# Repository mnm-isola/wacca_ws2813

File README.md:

# WACCA WS2813 LED PCB Replacement

---

# WARNING: USE AT YOUR OWN RISK

---

## BOM (for use with WS2813E / WS2813B-V4 or below)

| Footprint | Parts                  | Size | Value  | LCSC    | Remark                                        |
| --------- | ---------------------- | ---- | ------ | ------- | --------------------------------------------- |
| C1-C8     | Decoupling Capacitors  | 0805 | 100nF  | C49678  |                                               |
| C9        | Electrolytic Capacitor | TBD  | 1000uF | TBD     | Optional. THT on rev1, SMD on later revisions |
| CN1,CN2   | JST XA 3 pin           |      |        | C265055 | B03B-XASK-1(LF)(SN)                           |
| CN3       | JST XA 4 pin           |      |        | C264994 | B04B-XASK-1(LF)(SN)                           |
| D1-D8     | Worldsemi WS2813E      |      |        | C160214 |                                               |
| R1,R2     |                        | 0805 | 100R   | C17408  |                                               |
| U1,U2     | MMBD1503A              |      |        | C242273 |                                               |

---

## BOM (for use with WS2813B-V5)

| Footprint | Parts                  | Size | Value  | LCSC    | Remark                                        |
| --------- | ---------------------- | ---- | ------ | ------- | --------------------------------------------- |
| C1-C8     |                        |      |        |         | WS2813B-V5 do not require decoupling caps     |
| C9        | Electrolytic Capacitor | TBD  | 1000uF | TBD     | Optional. THT on rev1, SMD on later revisions |
| CN1,CN2   | JST XA 3 pin           |      |        | C265055 | B03B-XASK-1(LF)(SN)                           |
| CN3       | JST XA 4 pin           |      |        | C264994 | B04B-XASK-1(LF)(SN)                           |
| D1-D8     | Worldsemi WS2813B-V5   |      |        | C965558 |                                               |
| R1,R2     |                        | 0805 | 100R   | C17408  |                                               |
| U1,U2     | MMBD1503A              |      |        | C242273 |                                               |

## Manufracturing warnings

[Datasheet of WS2813](https://pdf1.alldatasheet.com/datasheet-pdf/view/1134580/WORLDSEMI/WS2813.html)

According to page 7: These LEDs are moisture sensitive, they need to be baked and dried before SMT assembly. Not all PCB fabs have this procedure  (eg JLCPCB's economic option), **be sure to consult and notify the fab of your choice before mass producing the PCBs, otherwise you may end up with extremely high failure rate**. (I learnt it the hard way so you don't have to.)

PCB thickness: 1.6mm

Color: White

---

##### What about a WS2812 clone?

I don't feel like spending time on a inferior design so no.

---

## Licensing

This project is under the [GNU General Public License v3.0](LICENSE.md).

- Commercial use of this project is allowed (i.e. you can go fab these designs and sell them for profit)

- Modifications based on this project needs to be open sourced under the GPLv3 license.

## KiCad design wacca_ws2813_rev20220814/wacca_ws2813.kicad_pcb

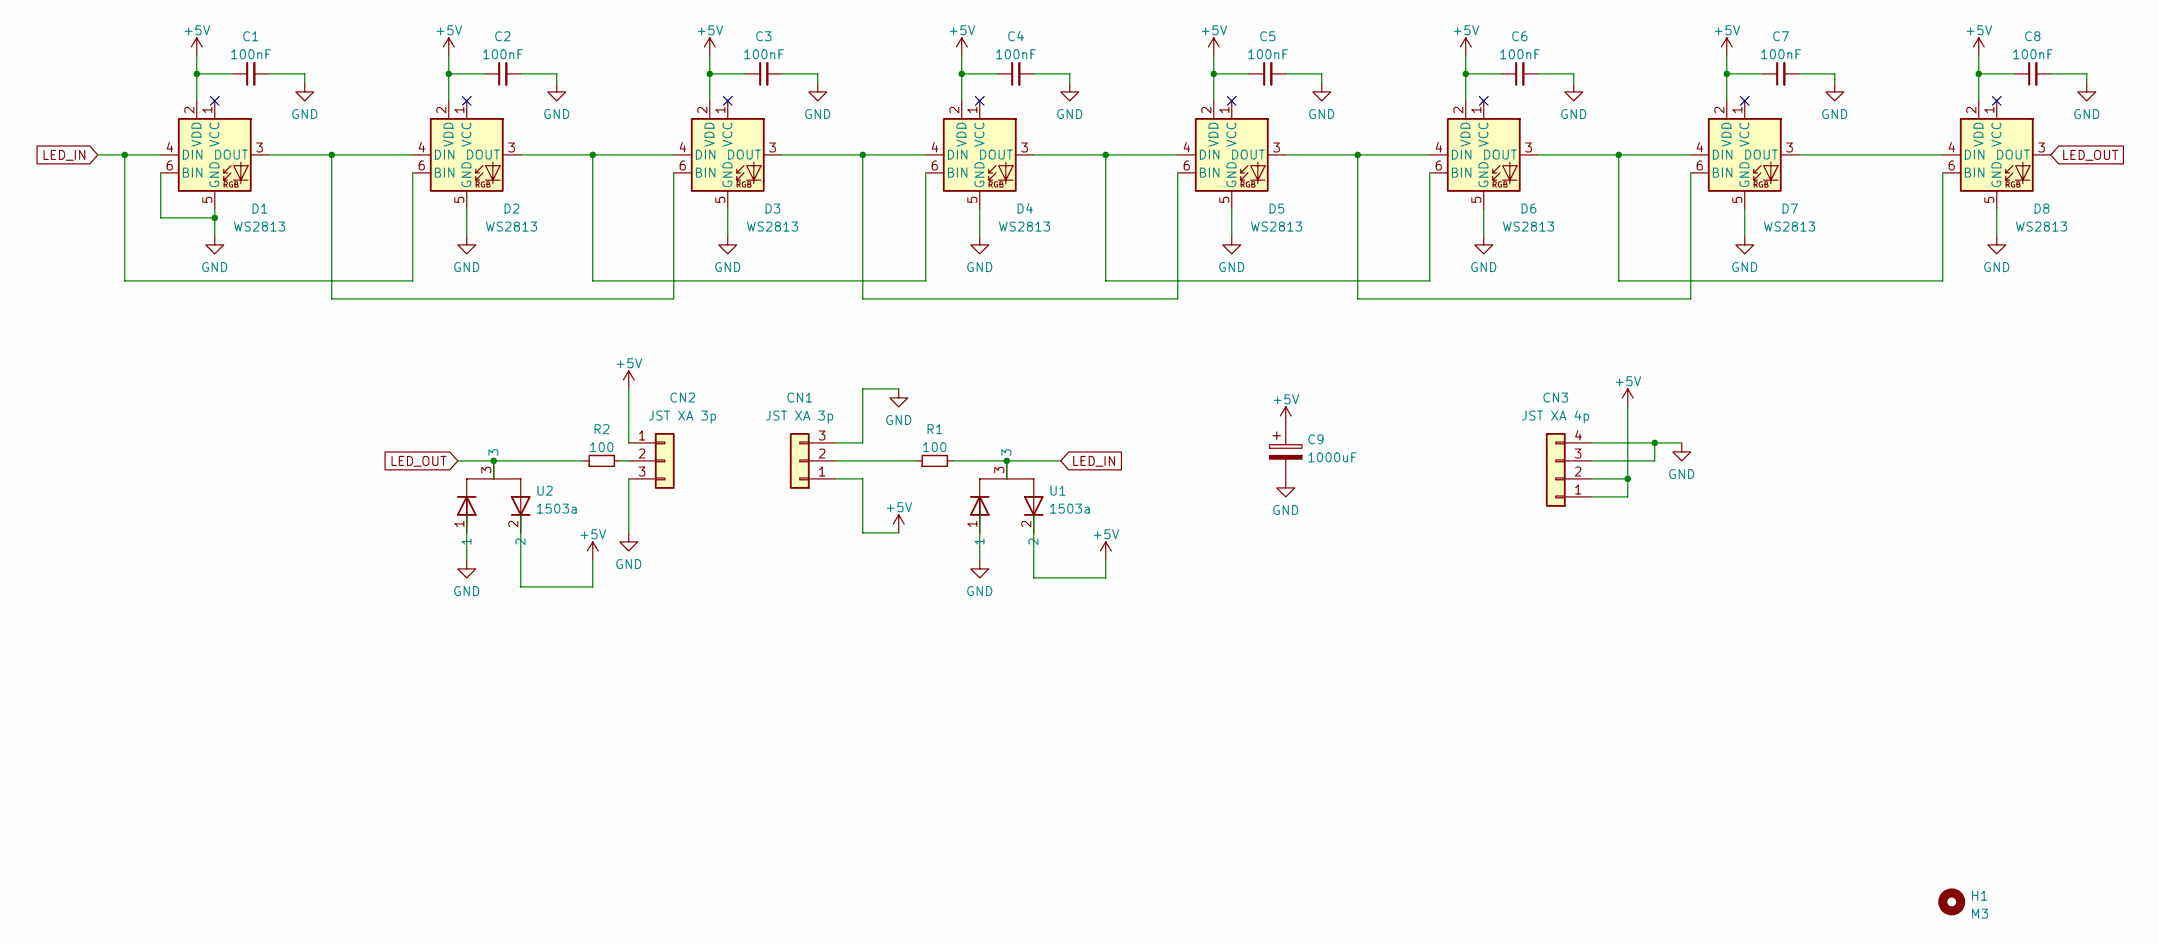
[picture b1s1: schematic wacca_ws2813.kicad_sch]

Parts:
C1, C2, C3, C4, C5, C6, C7, C8: 100nF; C_0805_2012Metric_Pad1.18x1.45mm_HandSolder
C9: 1000uF; CP_Elec_6.3x5.2
CN1, CN2: JST XA 3p; JST_XA_B03B-XASK-1_1x03_P2.50mm_Vertical
CN3: JST XA 4p; JST_XA_B04B-XASK-1_1x04_P2.50mm_Vertical
D1, D2, D3, D4, D5, D6, D7, D8: WS2813; LED_WS2812_PLCC6_5.0x5.0mm_P1.6mm
H1: M3; MountingHole_3.2mm_M3
R1, R2: 100; R_0805_2012Metric_Pad1.20x1.40mm_HandSolder
U1, U2: 1503a; TSOT-23_HandSoldering

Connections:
+5V: C1.1, C2.1, C3.1, C4.1, C5.1, C6.1, C7.1, C8.1, C9.1, CN1.1, CN2.1, CN3.1, CN3.2, D1.2 (VDD), D2.2 (VDD), D3.2 (VDD), D4.2 (VDD), D5.2 (VDD), D6.2 (VDD), D7.2 (VDD), D8.2 (VDD), U1.2, U2.2
GND: C1.2, C2.2, C3.2, C4.2, C5.2, C6.2, C7.2, C8.2, C9.2, CN1.3, CN2.3, CN3.3, CN3.4, D1.5 (GND), D1.6 (BIN), D2.5 (GND), D3.5 (GND), D4.5 (GND), D5.5 (GND), D6.5 (GND), D7.5 (GND), D8.5 (GND), U1.1, U2.1
LED_IN: D1.4 (DIN), D2.6 (BIN), R1.2, U1.3
LED_OUT: D8.3 (DOUT), R2.1, U2.3
unnamed: CN1.2, R1.1
unnamed: CN2.2, R2.2
unnamed: D1.3 (DOUT), D2.4 (DIN), D3.6 (BIN)
unnamed: D2.3 (DOUT), D3.4 (DIN), D4.6 (BIN)
unnamed: D3.3 (DOUT), D4.4 (DIN), D5.6 (BIN)
unnamed: D4.3 (DOUT), D5.4 (DIN), D6.6 (BIN)
unnamed: D5.3 (DOUT), D6.4 (DIN), D7.6 (BIN)
unnamed: D6.3 (DOUT), D7.4 (DIN), D8.6 (BIN)
unnamed: D7.3 (DOUT), D8.4 (DIN)

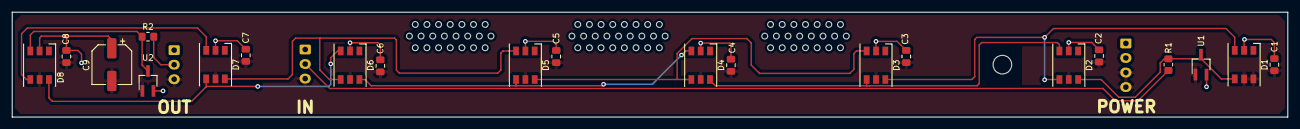
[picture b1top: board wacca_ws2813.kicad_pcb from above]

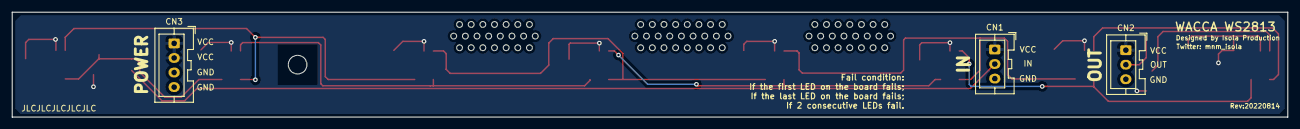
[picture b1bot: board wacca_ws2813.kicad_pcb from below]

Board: 2 copper layers, 219.0 x 18.0 mm, 25 parts (3 on the bottom side), 13 nets.

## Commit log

2022-09-01 a
    wah
2022-10-31 added rev20221021
